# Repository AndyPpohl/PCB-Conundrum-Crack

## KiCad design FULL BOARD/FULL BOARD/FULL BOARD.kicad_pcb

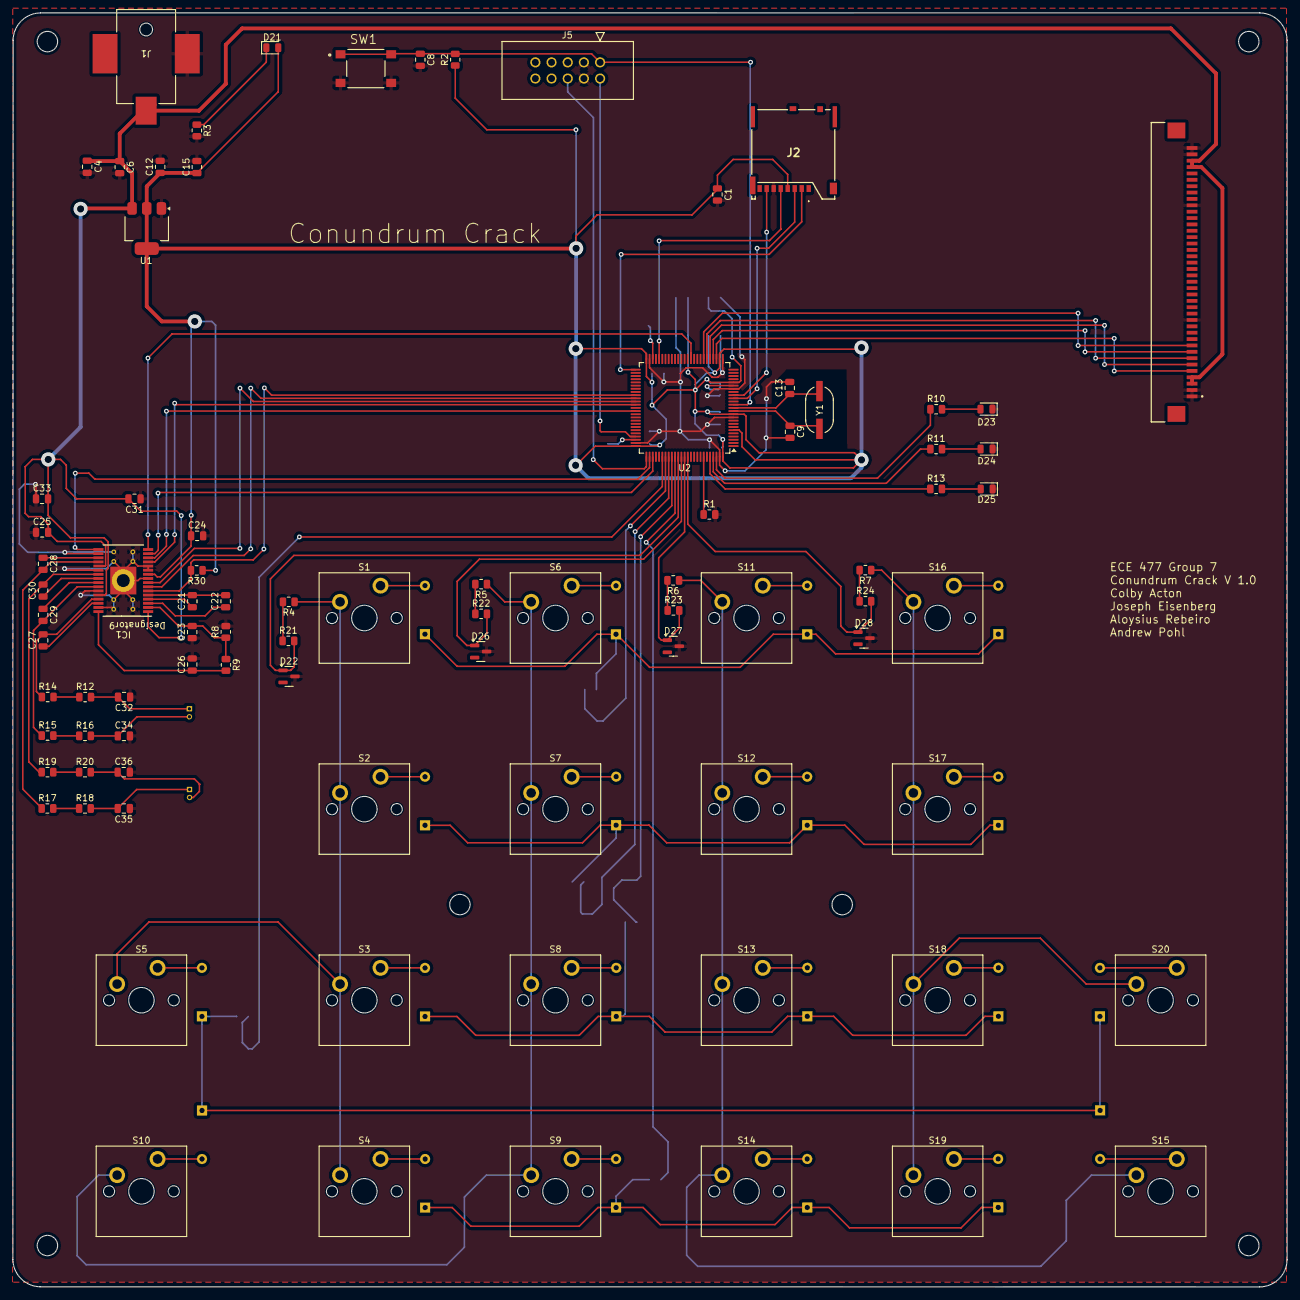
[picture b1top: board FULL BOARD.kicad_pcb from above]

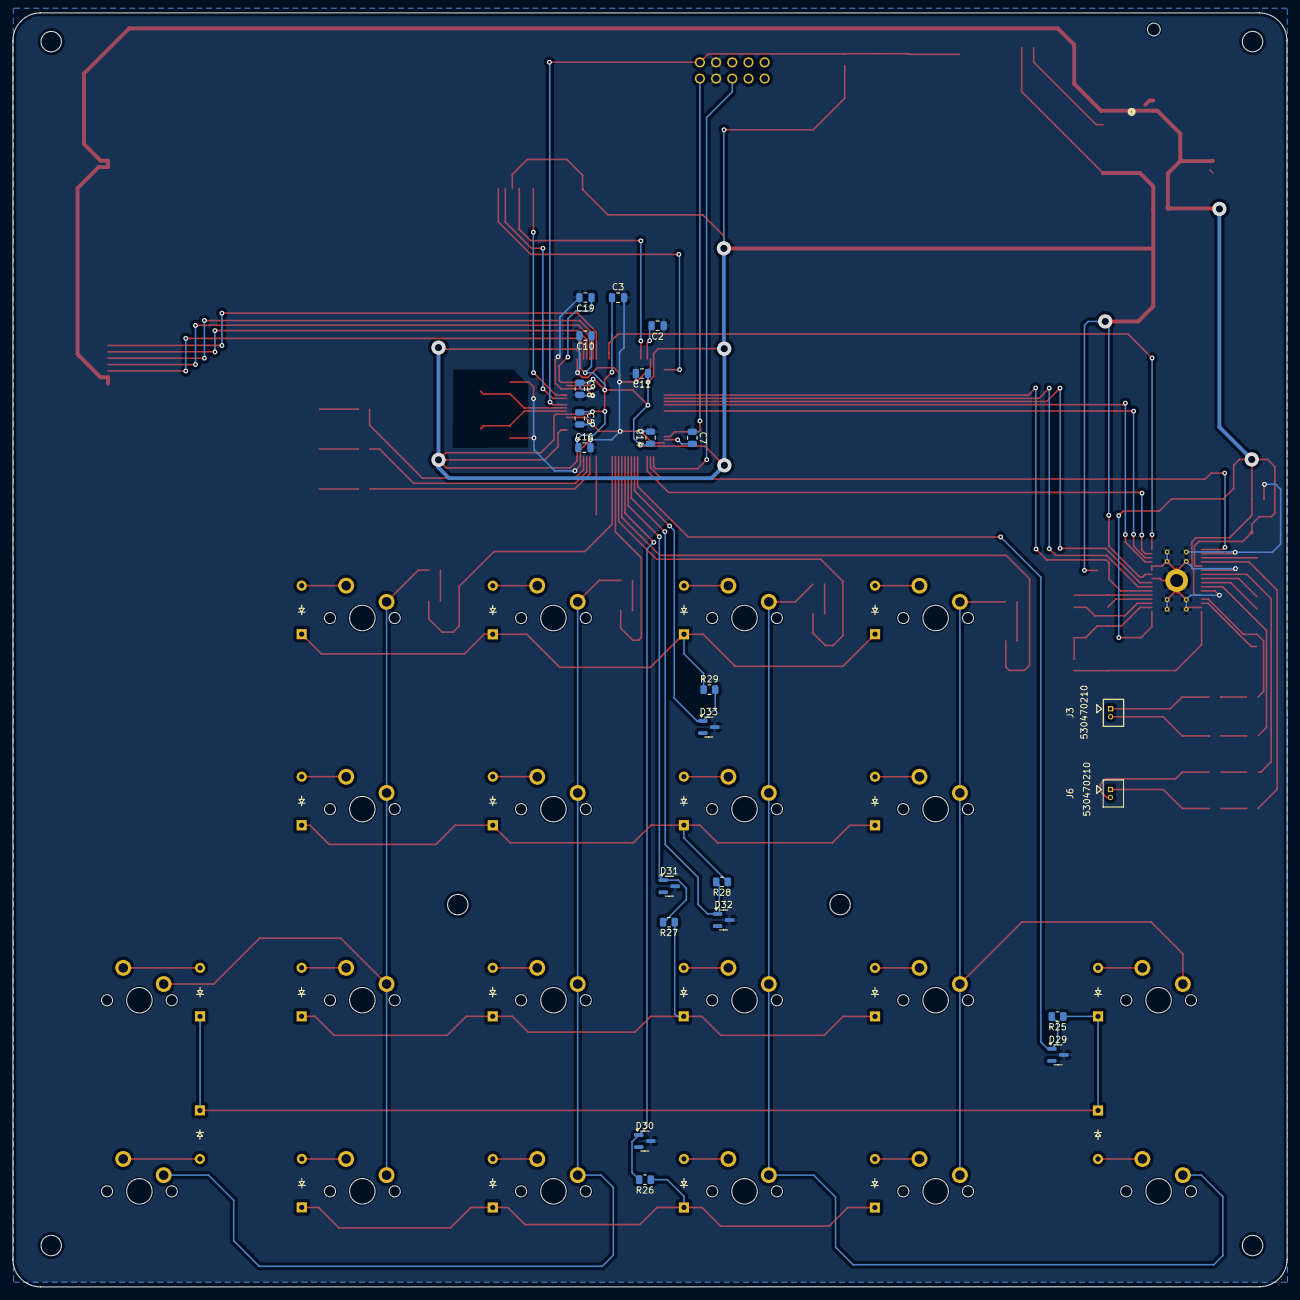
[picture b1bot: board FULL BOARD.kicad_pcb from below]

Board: 2 copper layers, 200.0 x 200.0 mm, 128 parts (42 on the bottom side), 98 nets.

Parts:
C1: 100uF; C_0805_2012Metric
C2, C7: 2.2uF; C_0805_2012Metric
C3: 4.7uF; C_0805_2012Metric
C4, C15: 22uF; C_0805_2012Metric
C5, C6, C8, C10, C11, C12, C14, C16, C18: 100nF; C_0805_2012Metric
C9, C13: 26pF; C_0805_2012Metric
C19, C21, C22, C23, C24, C26: 1uF; C_0805_2012Metric
C25, C31, C33: 10uF; C_0805_2012Metric
C27, C28, C29, C30: .22uF; C_0805_2012Metric
C32, C34, C35, C36: 47nF; C_0805_2012Metric
D1, D2, D3, D4, D5, D6, D7, D8, D9, D10, D11, D12, D13, D14, D15, D16, D17, D18, D19, D20: Diode; Diode_DO-35
D21, D23, D24, D25: LED; LED_0805_2012Metric
D22, D26, D27, D28, D29, D30, D31, D32, D33: BZX84Cxx; SOT-23
IC1: TAS5760LDAP; DAP0032A_M
J1: PJ-036AH-SMT-TR; CONN3_PJ-036AH_CUD
J2: MEM2080-00-128-00-A; MEM20800012800A
J3, J6: B2B-PH-K-S; CON_530470210_MOL
J4: 5019514000; GCT_FFC3B07-40-T
J5: 61201021621; CONN_61201021621_WRE
R1: 100K; R_0805_2012Metric
R2: 100k; R_0805_2012Metric
R3, R4, R5, R6, R7: 1k; R_0805_2012Metric
R8: 47; R_0805_2012Metric
R9, R10, R11, R13, R30: 10k; R_0805_2012Metric
R12, R16, R18, R20: 68; R_0805_2012Metric
R14, R15, R17, R19, R21, R22, R23, R24, R25, R26, R27, R28, R29: 100; R_0805_2012Metric
S1, S2, S3, S4, S5, S6, S7, S8, S9, S10, S11, S12, S13, S14, S15, S16, S17, S18, S19, S20: Keyswitch; MX_PCB_1.00u
SW1: PTS645SK50SMTR92LFS; SW_PTS645SK50SMTR92LFS
U1: LD1117S33TR_SOT223; SOT-223-3_TabPin2
U2: STM32H743VITx; LQFP-100_14x14mm_P0.5mm
Y1: ABLS7M2-16.000MHZ-D-2Y-T; XTAL_ABLS7M2_ABR

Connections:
+3.3V: C1.1, C3.1, C5.1, C10.1, C11.1, C12.1, C14.1, C15.1, C16.1, C18.1, C19.1, C24.1, D21.2 (A), IC1.10 (DVDD), J2.4 (VDD), R2.1, R30.1, U1.2 (VO), U2.6 (VBAT), U2.11 (VDD), U2.20 (VREF+), U2.21 (VDDA), U2.27 (VDD), U2.50 (VDD), U2.75 (VDD), U2.100 (VDD)
+5V: C4.1, C6.1, C25.2, C31.2, C33.2, IC1.1 (AVDD), IC1.21 (PVDD_1), IC1.28 (PVDD_2), J1.1, J4.3, J4.4, J4.37, J4.38, U1.3 (VI)
/BOOT0: R1.1, U2.94 (BOOT0)
/HSE_IN: C9.1, U2.12 (PH0), Y1.1
/HSE_OUT: C13.1, U2.13 (PH1), Y1.2
/LCD_CS: J4.5, U2.28 (PA4)
/LCD_MISO: J4.6, U2.30 (PA6)
/LCD_MOSI: J4.7, U2.31 (PA7)
/LCD_SCK: J4.8, U2.29 (PA5)
/NRST: C8.1, J5.1, R2.2, SW1.1, SW1.2, U2.14 (NRST)
/SD_CLK: J2.5 (CLK), U2.46 (PB10)
/SD_CS: J2.2 (CD/DAT3), U2.51 (PB12)
/SD_DI: J2.3 (CMD), U2.16 (PC1)
/SD_DO: J2.7 (DAT0), U2.17 (PC2_C)
/SWC: J5.6, U2.76 (PA14)
/SWDIO: J5.2, U2.72 (PA13)
/VCAP1: C2.2, U2.48 (VCAP)
/VCAP2: C7.2, U2.73 (VCAP)
Col 1: D22.1 (A), R21.2, U2.86 (PD5)
Col 2: D26.1 (A), R22.2, U2.87 (PD6)
Col 3: D27.1 (A), R23.2, U2.88 (PD7)
Col 4: D28.1 (A), R24.2, U2.89 (PB3)
FREQ: IC1.8 (FREQ/SDA), U2.61 (PD14)
GND: C1.2, C2.1, C3.2, C4.2, C5.2, C6.2, C7.1, C8.2, C9.2, C10.2, C11.2, C12.2, C13.2, C14.2, C15.2, C16.2, C18.2, C19.2, C23.1, C24.2, C25.1, C26.2, C31.1, C32.1, C33.1, C34.2, C35.1, C36.2, D22.3 (K), D23.1 (K), D24.1 (K), D25.1 (K), D26.3 (K), D27.3 (K), D28.3 (K), D29.3 (K), D30.3 (K), D31.3 (K), D32.3 (K), D33.3 (K), IC1.9 (PBTL/SCL), IC1.11 (SPK_GAIN0), IC1.12 (SPK_GAIN1), IC1.18 (DGND), IC1.22 (PGND_1), IC1.27 (PGND_2), IC1.31 (GGND), IC1.33 (EP), IC1.V, J1.2, J2.6 (VSS), J4.1, J4.2, J4.13, J4.31, J4.39, J4.40, J5.3, J5.4, R1.2, R3.2, R8.2, SW1.3, SW1.4, U1.1 (GND), U2.10 (VSS), U2.19 (VSSA), U2.26 (VSS), U2.49 (VSS), U2.74 (VSS), U2.99 (VSS)
I2S_CK: IC1.15 (SCLK), U2.78 (PC10)
I2S_MCLK: IC1.14 (MCLK), U2.64 (PC7)
I2S_SD: IC1.16 (SDIN), U2.36 (PB2)
I2S_WS: IC1.17 (LRCK), U2.77 (PA15)
unnamed: C32.2, J3.1, R12.2
unnamed: C34.1, J3.2, R16.2
unnamed: C35.2, J6.1, R18.2
unnamed: C36.1, J6.2, R20.2
unnamed: D1.2 (A), S5.2
unnamed: D1.1 (K), D6.1 (K), D11.1 (K), D16.1 (K), R25.1
unnamed: D2.2 (A), S1.2
unnamed: D3.2 (A), S2.2
unnamed: D4.2 (A), S3.2
unnamed: D5.2 (A), S4.2
unnamed: D6.2 (A), S10.2
unnamed: D7.2 (A), S6.2
unnamed: D8.2 (A), S7.2
unnamed: D9.2 (A), S8.2
unnamed: D10.2 (A), S9.2
unnamed: D5.1 (K), D10.1 (K), D15.1 (K), D20.1 (K), R26.1
unnamed: D11.2 (A), S15.2
unnamed: D12.2 (A), S11.2
unnamed: D2.1 (K), D7.1 (K), D12.1 (K), D17.1 (K), R29.1
unnamed: D13.2 (A), S12.2
unnamed: D3.1 (K), D8.1 (K), D13.1 (K), D18.1 (K), R28.1
unnamed: D14.2 (A), S13.2
unnamed: D4.1 (K), D9.1 (K), D14.1 (K), D19.1 (K), R27.1
unnamed: D15.2 (A), S14.2
unnamed: D16.2 (A), S20.2
unnamed: D17.2 (A), S16.2
unnamed: D18.2 (A), S17.2
unnamed: D19.2 (A), S18.2
unnamed: D20.2 (A), S19.2
unnamed: D21.1 (K), R3.1
unnamed: D23.2 (A), R10.2
unnamed: D24.2 (A), R11.2
unnamed: D25.2 (A), R13.2
unnamed: C21.2, C22.2, IC1.5 (ANA_REF)
unnamed: C22.1, IC1.3 (ANA_REG)
unnamed: C27.1, IC1.30 (BSTRPA+)
unnamed: C29.1, IC1.25 (BSTRPA-)
unnamed: C28.1, IC1.19 (BSTRPB+)
unnamed: C30.1, IC1.24 (BSTRPB-)
unnamed: C26.1, IC1.32 (GVDD_REG), R9.2
unnamed: C23.2, IC1.2 (SFT_CLIP), R8.1, R9.1
unnamed: C27.2, IC1.29 (SPK_OUTA+), R14.1
unnamed: C29.2, IC1.26 (SPK_OUTA-), R15.1
unnamed: C28.2, IC1.20 (SPK_OUTB+), R17.1
unnamed: C30.2, IC1.23 (SPK_OUTB-), R19.1
unnamed: C21.1, IC1.4 (VCOM)
unnamed: R4.1, S1.1, S2.1, S3.1, S4.1, S5.1
unnamed: R5.1, S6.1, S7.1, S8.1, S9.1, S10.1
unnamed: R6.1, S11.1, S12.1, S13.1, S14.1, S15.1
unnamed: R7.1, S16.1, S17.1, S18.1, S19.1, S20.1
unnamed: R12.1, R14.2
unnamed: R15.2, R16.1
unnamed: R17.2, R18.1
unnamed: R19.2, R20.1
unnamed: R4.2, R21.1
unnamed: R5.2, R22.1
unnamed: R6.2, R23.1
unnamed: R7.2, R24.1
unnamed: R13.1, U2.96 (PB9)
unnamed: R11.1, U2.97 (PE0)
unnamed: R10.1, U2.98 (PE1)
Row 1: D33.1 (A), R29.2, U2.82 (PD1)
Row 2: D32.1 (A), R28.2, U2.83 (PD2)
Row 3: D31.1 (A), R27.2, U2.84 (PD3)
Row 4: D30.1 (A), R26.2, U2.85 (PD4)
Row 5: D29.1 (A), R25.2, U2.81 (PD0)
SPK_FAULT: IC1.6 (~SPK_FAULT), R30.2, U2.59 (PD12)
SPK_SD: IC1.7 (~SPK_SD), U2.60 (PD13)
SPK_SLEEP: IC1.13 (SPK_SLEEP/ADR), U2.62 (PD15)
Wait: J4.9, U2.32 (PC4)

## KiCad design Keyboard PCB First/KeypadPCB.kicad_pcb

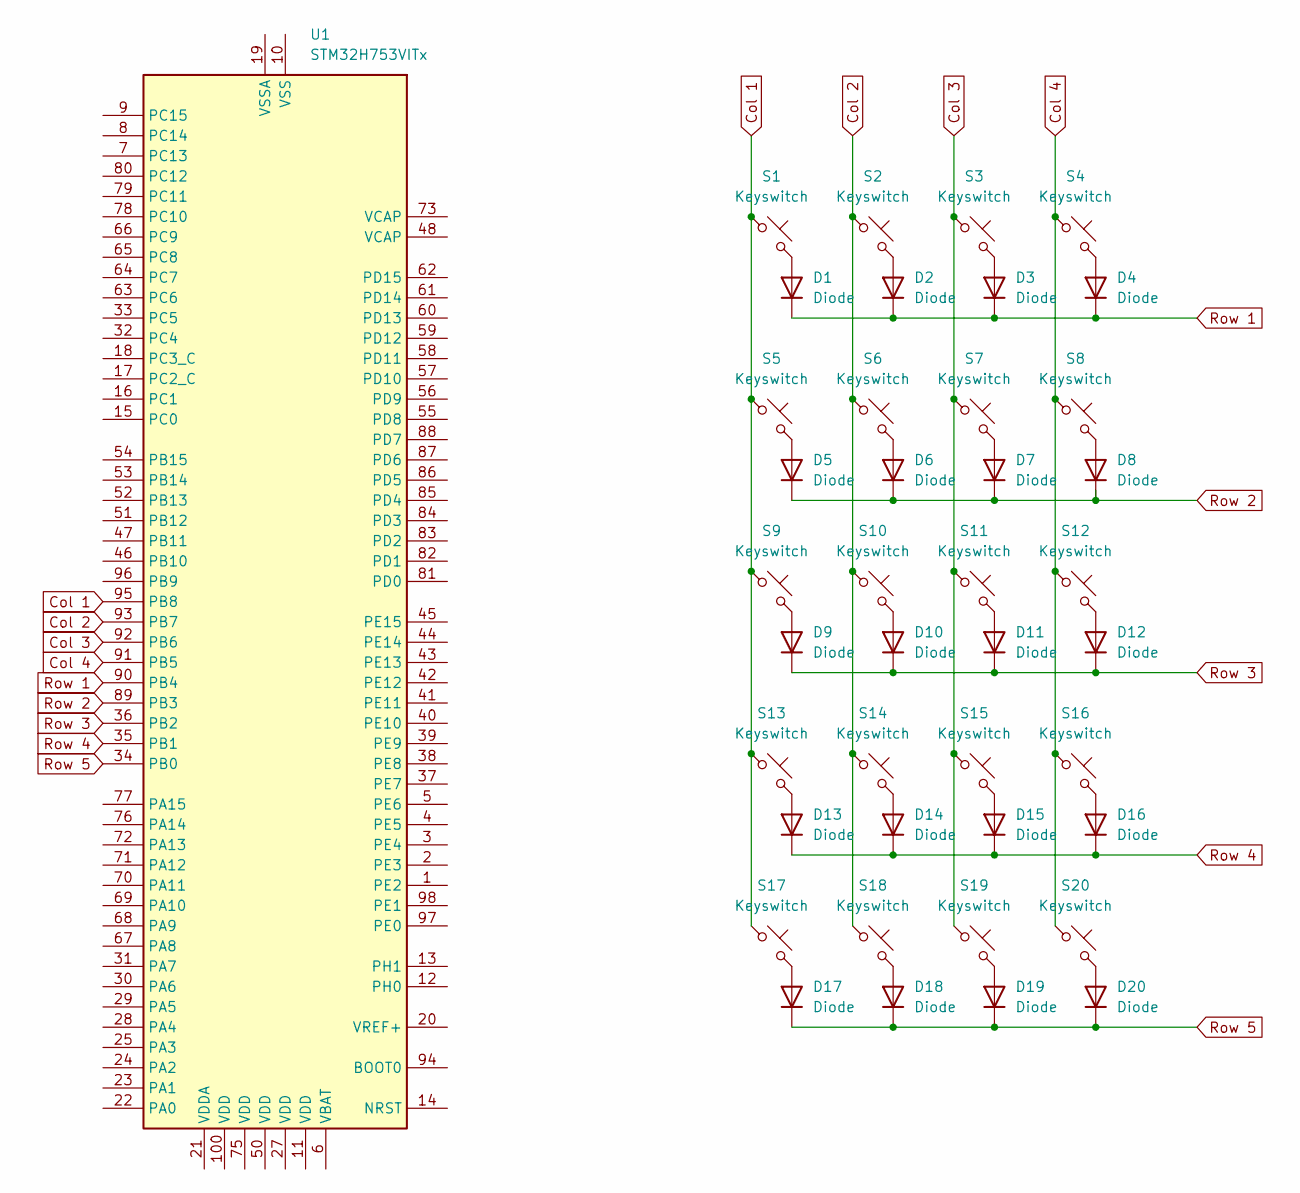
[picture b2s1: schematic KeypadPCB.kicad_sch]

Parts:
D1, D2, D3, D4, D5, D6, D7, D8, D9, D10, D11, D12, D13, D14, D15, D16, D17, D18, D19, D20: Diode; Diode_DO-35
S1, S2, S3, S4, S5, S6, S7, S8, S9, S10, S11, S12, S13, S14, S15, S16, S17, S18, S19, S20: Keyswitch; MX_PCB_1.00u
U1: STM32H753VITx; LQFP-100_14x14mm_P0.5mm

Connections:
Col 1: S1.1, S5.1, S9.1, S13.1, S17.1, U1.95 (PB8)
Col 2: S2.1, S6.1, S10.1, S14.1, S18.1, U1.93 (PB7)
Col 3: S3.1, S7.1, S11.1, S15.1, S19.1, U1.92 (PB6)
Col 4: S4.1, S8.1, S12.1, S16.1, S20.1, U1.91 (PB5)
unnamed: D1.2 (A), S1.2
unnamed: D2.2 (A), S2.2
unnamed: D3.2 (A), S3.2
unnamed: D4.2 (A), S4.2
unnamed: D5.2 (A), S5.2
unnamed: D6.2 (A), S6.2
unnamed: D7.2 (A), S7.2
unnamed: D8.2 (A), S8.2
unnamed: D9.2 (A), S9.2
unnamed: D10.2 (A), S10.2
unnamed: D11.2 (A), S11.2
unnamed: D12.2 (A), S12.2
unnamed: D13.2 (A), S13.2
unnamed: D14.2 (A), S14.2
unnamed: D15.2 (A), S15.2
unnamed: D16.2 (A), S16.2
unnamed: D17.2 (A), S17.2
unnamed: D18.2 (A), S18.2
unnamed: D19.2 (A), S19.2
unnamed: D20.2 (A), S20.2
unnamed: U1.10 (VSS), U1.26 (VSS), U1.49 (VSS), U1.74 (VSS), U1.99 (VSS)
Row 1: D1.1 (K), D2.1 (K), D3.1 (K), D4.1 (K), U1.90 (PB4)
Row 2: D5.1 (K), D6.1 (K), D7.1 (K), D8.1 (K), U1.89 (PB3)
Row 3: D9.1 (K), D10.1 (K), D11.1 (K), D12.1 (K), U1.36 (PB2)
Row 4: D13.1 (K), D14.1 (K), D15.1 (K), D16.1 (K), U1.35 (PB1)
Row 5: D17.1 (K), D18.1 (K), D19.1 (K), D20.1 (K), U1.34 (PB0)

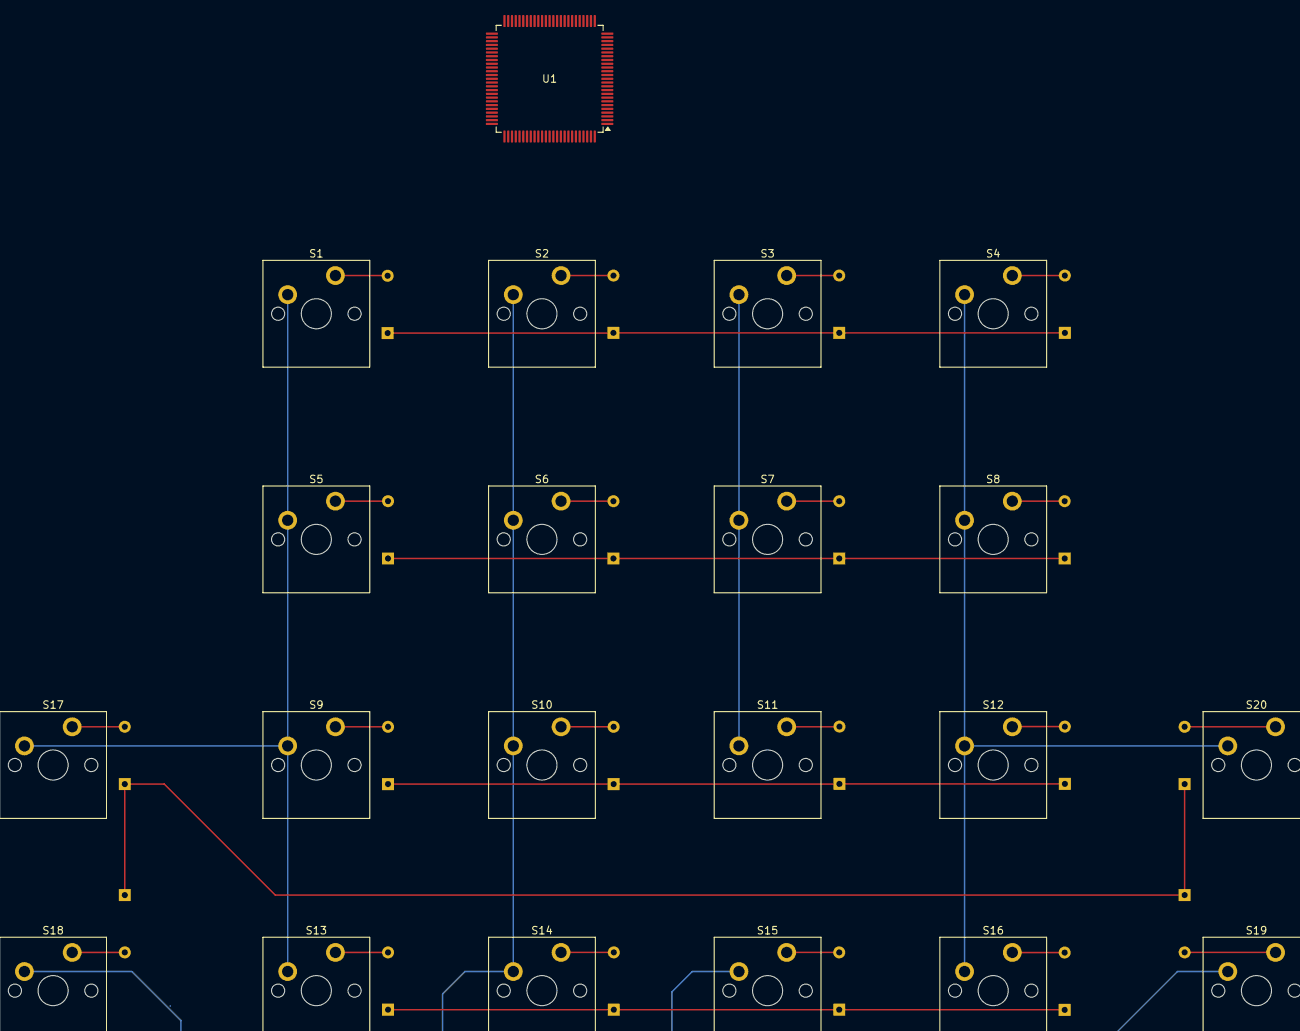
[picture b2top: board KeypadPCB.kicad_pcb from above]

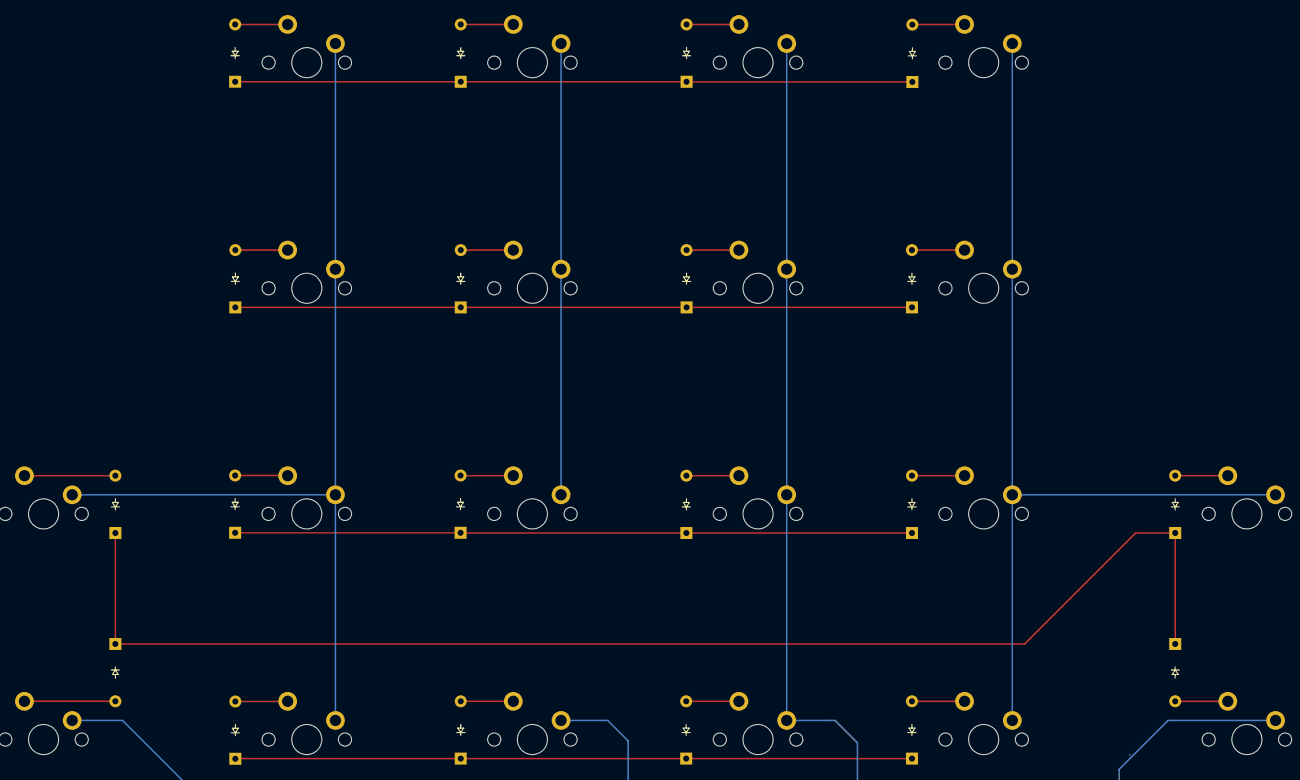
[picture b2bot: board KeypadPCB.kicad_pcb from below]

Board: 2 copper layers, 41 parts (20 on the bottom side), 30 nets.

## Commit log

2024-09-19 Add keyboard KiCAD files
2024-09-19 Add Keyboard footprints and schematics
2024-09-26 initial full board
2024-09-27 schematic done
2024-09-27 schematics done with errors checked
2024-09-28 schematics done with errors checked1
2024-09-29 Push second keypad schematic
2024-10-02 amp schematic added
2024-10-02 updated schematic
2024-10-03 some routing done
2024-10-04 nearly complete PCB
2024-10-06 power and audio routing added, needs to be checked
2024-10-07 final(?) PCB before presentation
2024-10-08 Gerber added, 3D CAD added
2024-10-10 updated to most recent version
2024-10-10 Made some changes, not all made
2024-10-10 Updated micro routing, not finished
2024-10-11 Rerouted board
2024-10-13 updated footprints
2024-10-14 thrown changes
2024-10-15 changed LCD footprint, GNDA
2024-10-15 changed ribbon pins
2024-10-16 added filters and sleep
2024-10-16 changed amp via
2024-10-16 parts moved
2024-10-16 added names
2024-10-16 moved sd and lcd
2024-10-17 trash
2024-10-22 moved parts
2024-10-22 changed reset footprint
2024-10-22 change SD
2024-10-23 Added Gerber
2024-10-23 adjusted audio amp
2024-10-24 most feedback changes made
2024-10-24 Finished changes(?)
2024-11-06 Final board ordered
